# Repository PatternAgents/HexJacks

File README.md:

# HexJacks { ERA : Sixteen (16) Jack I/O board for Eurorack }

Format : ERA / Eurorack / Breadboard Friendly

Height : 1U 

Width: 16HP

Depth : 1.0 cm

Power : (Passive - no power requirements)

HexJacks is a simple sixteen (16) Jack I/O module,
where any Jack can either be used as an input or an output.
Optionally, J9 thru J12 can be populated with pushbuttons for inputs,
and J13 thru J16 can be populated with 3mm LEDs for indicator outputs.

[HexJacks](https://github.com/patternagents/HexJacks)

HexJacks can be used on a breadboard for prototyping new circuits,
or it can mounted into a 1U Rack system using the following 1U x 16 HP front panel design.

[HexJacks 1U Front Panel](https://github.com/patternagents/HexJacks)

HexJacks can be used in combination with two (2) or more other ERA modules
for mounting in a 3U ERA or Eurorack format card or even larger rack format

**thingSoC Reference Designs** are example thingSoC implementations that implement
various reference and testing circuits for demonstrating the use of the thingSoC libraries.
These reference designs can serve as starting templates for user designs.

---------------------------------------

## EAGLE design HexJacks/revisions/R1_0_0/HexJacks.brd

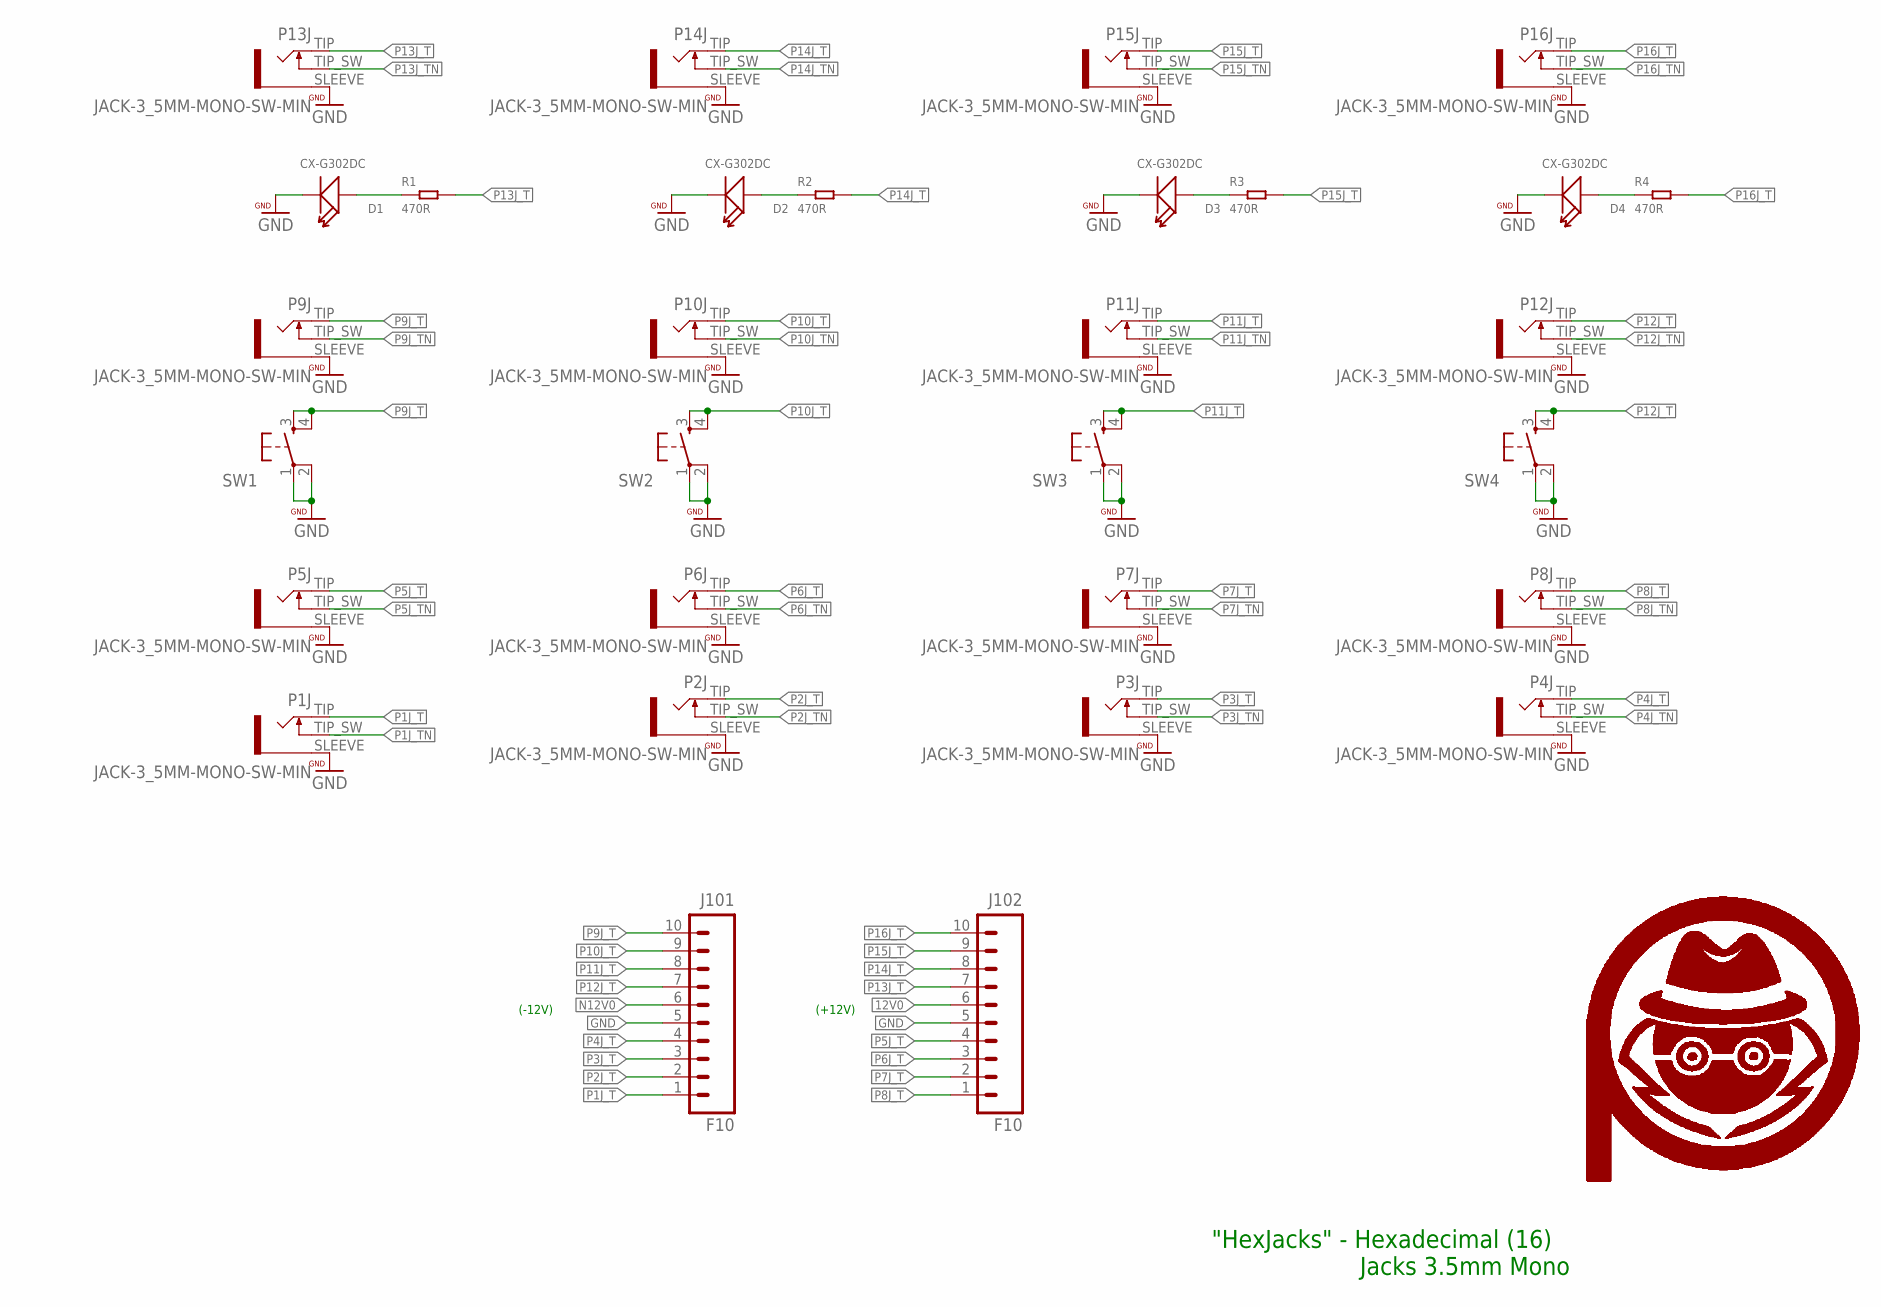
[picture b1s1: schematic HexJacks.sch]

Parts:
D1, D2, D3, D4: CX-G302DC; LED2-2.54-D3.0MM
J101, J102: F10; 1X10_OCTO
P1J, P2J, P3J, P4J, P5J, P6J, P7J, P8J, P9J, P10J, P11J, P12J, P13J, P14J, P15J, P16J: JACK-3_5MM-MONO-SW-MIN; WQP_PJ301M-MIN
R1, R2, R3, R4: 470R; R0603
SW1, SW2, SW3, SW4: TAC_SWITCHPTH; TACTILE-PTH
U$25, U$26, U$27, U$28: PA_LOGO_SYMSMALL; PA_LOGO_AGENT_SMALL_SYM

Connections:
12V0: J102.6
GND: D1.K (-), D2.K (-), D3.K (-), D4.K (-), J101.5, J102.5, P1J.SLEEVE, P2J.SLEEVE, P3J.SLEEVE, P4J.SLEEVE, P5J.SLEEVE, P6J.SLEEVE, P7J.SLEEVE, P8J.SLEEVE, P9J.SLEEVE, P10J.SLEEVE, P11J.SLEEVE, P12J.SLEEVE, P13J.SLEEVE, P14J.SLEEVE, P15J.SLEEVE, P16J.SLEEVE, SW1.1, SW1.2, SW2.1, SW2.2, SW3.1, SW3.2, SW4.1, SW4.2
N12V0: J101.6
unnamed: D1.A (+), R1.1
unnamed: D2.A (+), R2.1
unnamed: D3.A (+), R3.1
unnamed: D4.A (+), R4.1
P1J_T: J101.1, P1J.TIP
P1J_TN: P1J.TIP_SW
P2J_T: J101.2, P2J.TIP
P2J_TN: P2J.TIP_SW
P3J_T: J101.3, P3J.TIP
P3J_TN: P3J.TIP_SW
P4J_T: J101.4, P4J.TIP
P4J_TN: P4J.TIP_SW
P5J_T: J102.4, P5J.TIP
P5J_TN: P5J.TIP_SW
P6J_T: J102.3, P6J.TIP
P6J_TN: P6J.TIP_SW
P7J_T: J102.2, P7J.TIP
P7J_TN: P7J.TIP_SW
P8J_T: J102.1, P8J.TIP
P8J_TN: P8J.TIP_SW
P9J_T: J101.10, P9J.TIP, SW1.3, SW1.4
P9J_TN: P9J.TIP_SW
P10J_T: J101.9, P10J.TIP, SW2.3, SW2.4
P10J_TN: P10J.TIP_SW
P11J_T: J101.8, P11J.TIP, SW3.3, SW3.4
P11J_TN: P11J.TIP_SW
P12J_T: J101.7, P12J.TIP, SW4.3, SW4.4
P12J_TN: P12J.TIP_SW
P13J_T: J102.7, P13J.TIP, R1.2
P13J_TN: P13J.TIP_SW
P14J_T: J102.8, P14J.TIP, R2.2
P14J_TN: P14J.TIP_SW
P15J_T: J102.9, P15J.TIP, R3.2
P15J_TN: P15J.TIP_SW
P16J_T: J102.10, P16J.TIP, R4.2
P16J_TN: P16J.TIP_SW

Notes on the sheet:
(+12V)
(-12V)
"HexJacks" - Hexadecimal (16) Jacks 3.5mm Mono

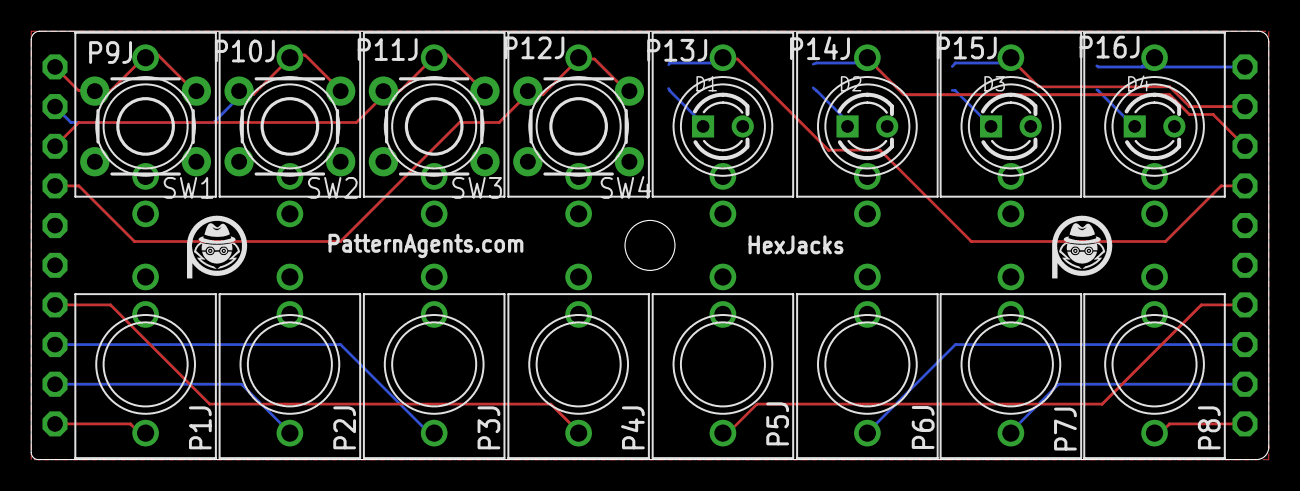
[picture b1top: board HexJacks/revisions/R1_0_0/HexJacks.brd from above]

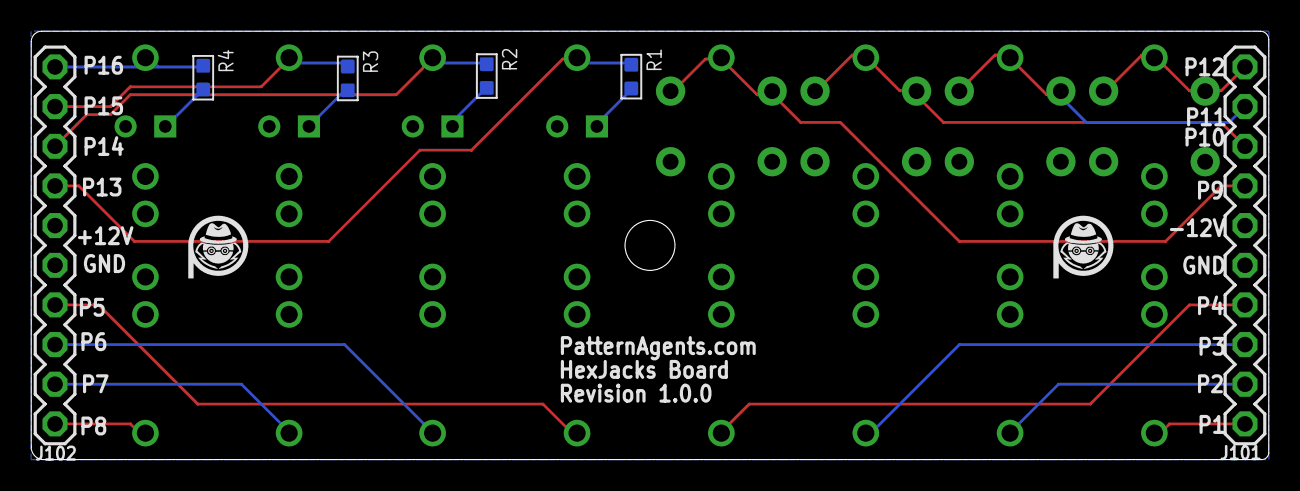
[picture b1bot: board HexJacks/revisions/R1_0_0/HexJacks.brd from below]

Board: 2 copper layers, 79.2 x 27.4 mm, 34 parts (8 on the bottom side), 21 nets.

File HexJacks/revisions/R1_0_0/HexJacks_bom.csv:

"Qty";"Value";"Device";"Package";"Parts";"Description";"";
"4";"";"TAC_SWITCHPTH";"TACTILE-PTH";"SW1, SW2, SW3, SW4";"Momentary Switch";"";
"4";"470R";"SMD-RES-470R-5%-1/10W(0603)";"R0603";"R1, R2, R3, R4";"301010088";"";
"4";"CX-G302DC";"DIP-LED-GREEN-GREEN(2P-D3MM)";"LED2-2.54-D3.0MM";"D1, D2, D3, D4";"304090040";"";
"2";"F10";"M10SILK_FEMALE_PTH";"1X10_OCTO";"J101, J102";"Header 10";"";
"16";"JACK-3_5MM-MONO-SW-MIN";"JACK-3_5MM-MONO-SW-MIN";"WQP_PJ301M-MIN";"P1J, P2J, P3J, P4J, P5J, P6J, P7J, P8J, P9J, P10J, P11J, P12J, P13J, P14J, P15J, P16J";"Jack, 3.5mm, RIght Angle, Though-Hole";"";
"4";"PA_LOGO_SYMSMALL";"PA_LOGO_SYMSMALL";"PA_LOGO_AGENT_SMALL_SYM";"U$25, U$26, U$27, U$28";"PatternAgents Logo Symbol";"";

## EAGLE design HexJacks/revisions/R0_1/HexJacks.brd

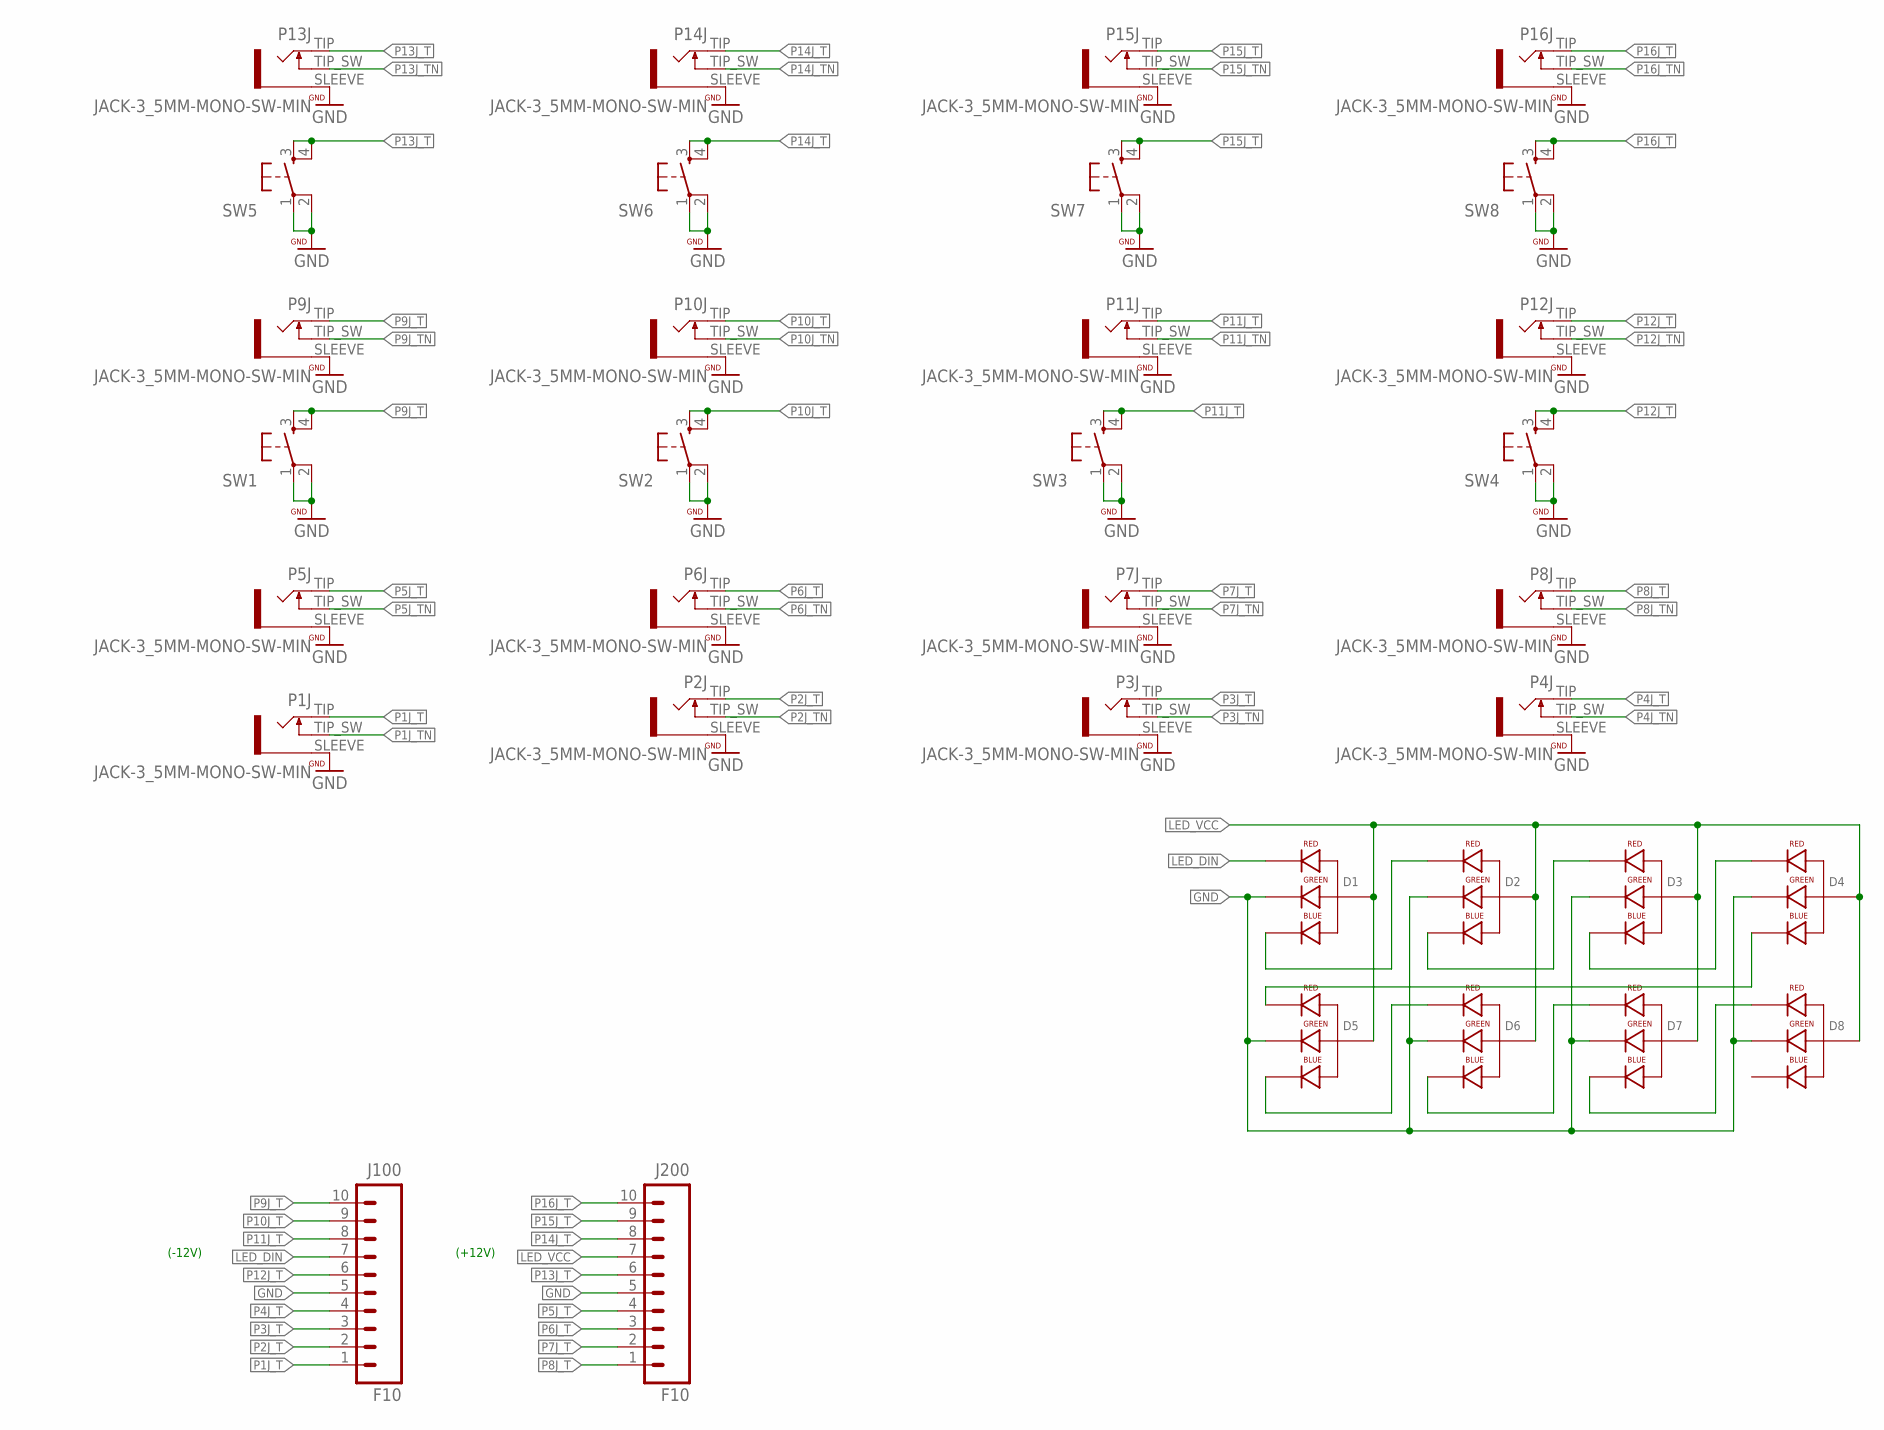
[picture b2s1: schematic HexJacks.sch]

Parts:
D1, D2, D3, D4, D5, D6, D7, D8: LED-RGB-CA-THRUCLEAR; LED-RGB-THRU
J100, J200: F10; 1X10_OCTO
P1J, P2J, P3J, P4J, P5J, P6J, P7J, P8J, P9J, P10J, P11J, P12J, P13J, P14J, P15J, P16J: JACK-3_5MM-MONO-SW-MIN; WQP_PJ301M-MIN
SW1, SW2, SW3, SW4, SW5, SW6, SW7, SW8: TAC_SWITCHPTH; TACTILE-PTH

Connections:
GND: D1.3 (GREEN_CATHODE), D2.3 (GREEN_CATHODE), D3.3 (GREEN_CATHODE), D4.3 (GREEN_CATHODE), D5.3 (GREEN_CATHODE), D6.3 (GREEN_CATHODE), D7.3 (GREEN_CATHODE), D8.3 (GREEN_CATHODE), J100.5, J200.5, P1J.SLEEVE, P2J.SLEEVE, P3J.SLEEVE, P4J.SLEEVE, P5J.SLEEVE, P6J.SLEEVE, P7J.SLEEVE, P8J.SLEEVE, P9J.SLEEVE, P10J.SLEEVE, P11J.SLEEVE, P12J.SLEEVE, P13J.SLEEVE, P14J.SLEEVE, P15J.SLEEVE, P16J.SLEEVE, SW1.1, SW1.2, SW2.1, SW2.2, SW3.1, SW3.2, SW4.1, SW4.2, SW5.1, SW5.2, SW6.1, SW6.2, SW7.1, SW7.2, SW8.1, SW8.2
LED_DIN: D1.1 (RED_CATHODE), J100.7
LED_VCC: D1.2 (ANODE), D2.2 (ANODE), D3.2 (ANODE), D4.2 (ANODE), D5.2 (ANODE), D6.2 (ANODE), D7.2 (ANODE), D8.2 (ANODE), J200.7
unnamed: D1.4 (BLUE_CATHODE), D2.1 (RED_CATHODE)
unnamed: D2.4 (BLUE_CATHODE), D3.1 (RED_CATHODE)
unnamed: D3.4 (BLUE_CATHODE), D4.1 (RED_CATHODE)
unnamed: D4.4 (BLUE_CATHODE), D5.1 (RED_CATHODE)
unnamed: D5.4 (BLUE_CATHODE), D6.1 (RED_CATHODE)
unnamed: D6.4 (BLUE_CATHODE), D7.1 (RED_CATHODE)
unnamed: D7.4 (BLUE_CATHODE), D8.1 (RED_CATHODE)
P1J_T: J100.1, P1J.TIP
P1J_TN: P1J.TIP_SW
P2J_T: J100.2, P2J.TIP
P2J_TN: P2J.TIP_SW
P3J_T: J100.3, P3J.TIP
P3J_TN: P3J.TIP_SW
P4J_T: J100.4, P4J.TIP
P4J_TN: P4J.TIP_SW
P5J_T: J200.4, P5J.TIP
P5J_TN: P5J.TIP_SW
P6J_T: J200.3, P6J.TIP
P6J_TN: P6J.TIP_SW
P7J_T: J200.2, P7J.TIP
P7J_TN: P7J.TIP_SW
P8J_T: J200.1, P8J.TIP
P8J_TN: P8J.TIP_SW
P9J_T: J100.10, P9J.TIP, SW1.3, SW1.4
P9J_TN: P9J.TIP_SW
P10J_T: J100.9, P10J.TIP, SW2.3, SW2.4
P10J_TN: P10J.TIP_SW
P11J_T: J100.8, P11J.TIP, SW3.3, SW3.4
P11J_TN: P11J.TIP_SW
P12J_T: J100.6, P12J.TIP, SW4.3, SW4.4
P12J_TN: P12J.TIP_SW
P13J_T: J200.6, P13J.TIP, SW5.3, SW5.4
P13J_TN: P13J.TIP_SW
P14J_T: J200.8, P14J.TIP, SW6.3, SW6.4
P14J_TN: P14J.TIP_SW
P15J_T: J200.9, P15J.TIP, SW7.3, SW7.4
P15J_TN: P15J.TIP_SW
P16J_T: J200.10, P16J.TIP, SW8.3, SW8.4
P16J_TN: P16J.TIP_SW

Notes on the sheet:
(+12V)
(-12V)

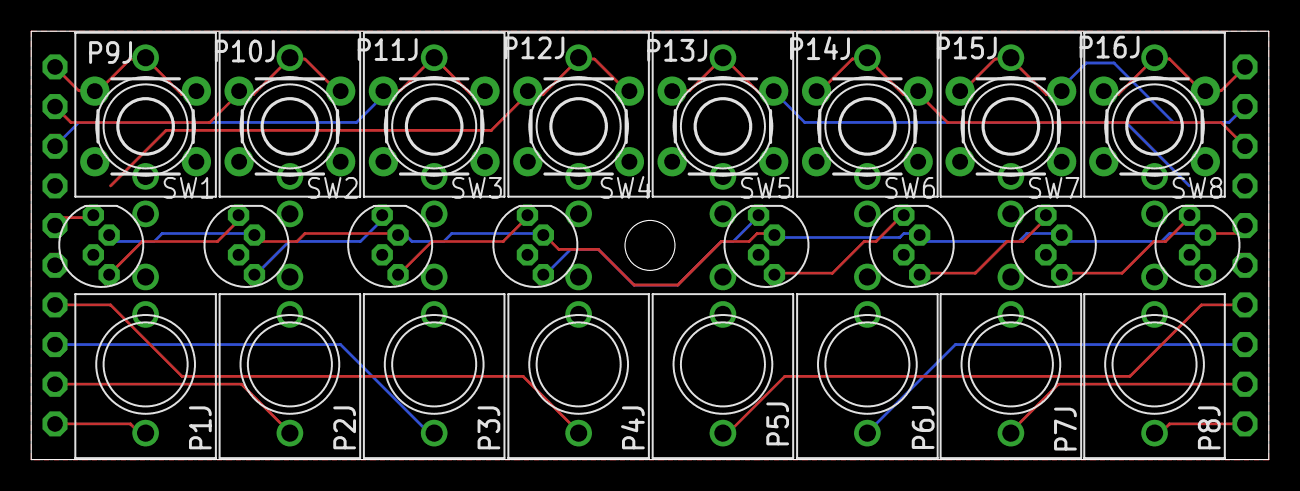
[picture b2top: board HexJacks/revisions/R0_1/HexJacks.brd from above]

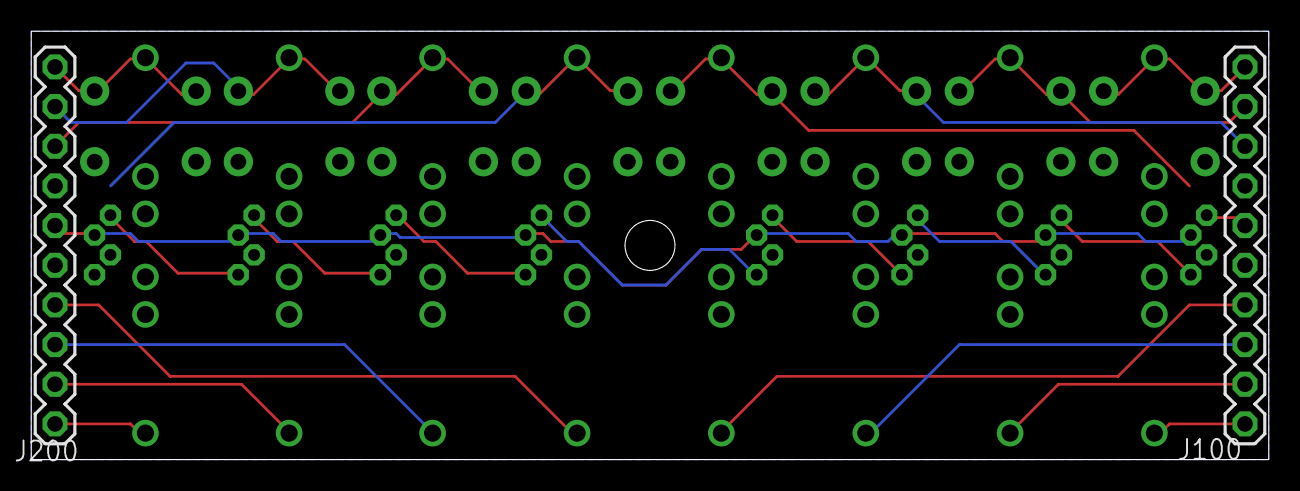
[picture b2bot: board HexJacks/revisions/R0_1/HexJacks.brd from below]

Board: 2 copper layers, 79.2 x 27.4 mm, 34 parts (2 on the bottom side), 26 nets.

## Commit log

2018-01-21 initial version
2018-03-27 revision 1.0.0

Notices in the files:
parts and their libraries:
PatternAgents-Beautify: License : http://creativecommons.org/licenses/by-sa/3.0
(Creative Commons 3.0)
